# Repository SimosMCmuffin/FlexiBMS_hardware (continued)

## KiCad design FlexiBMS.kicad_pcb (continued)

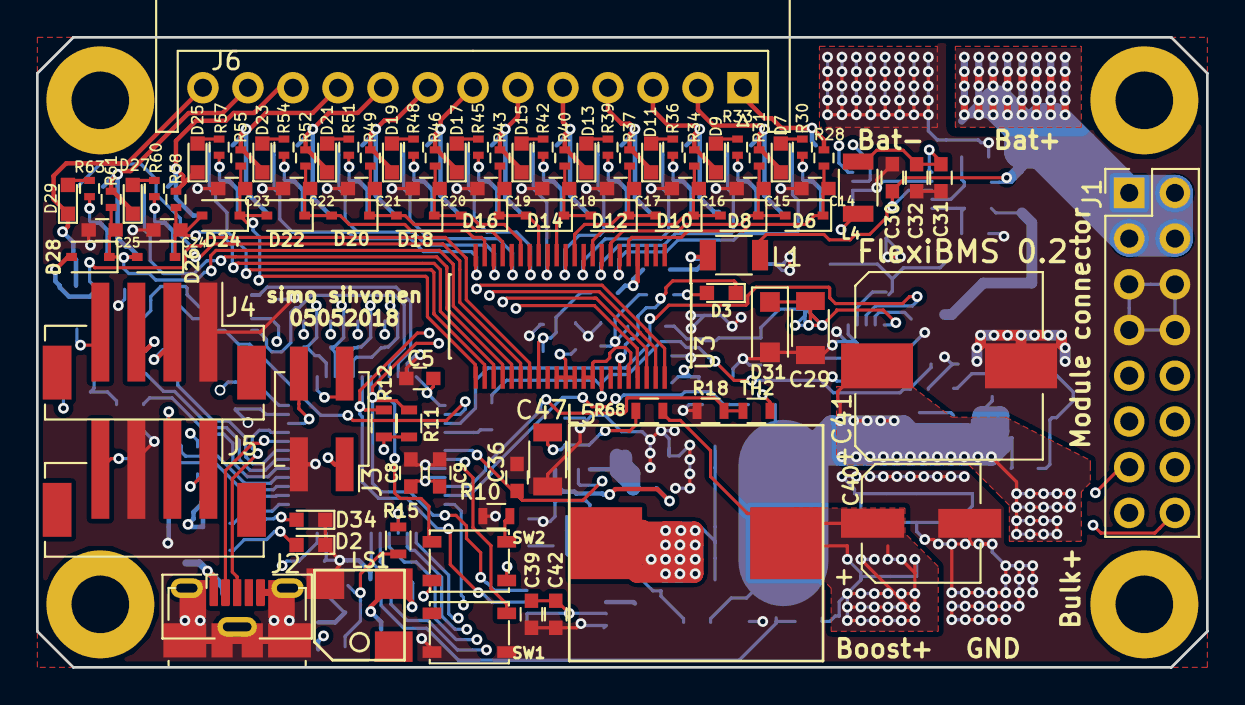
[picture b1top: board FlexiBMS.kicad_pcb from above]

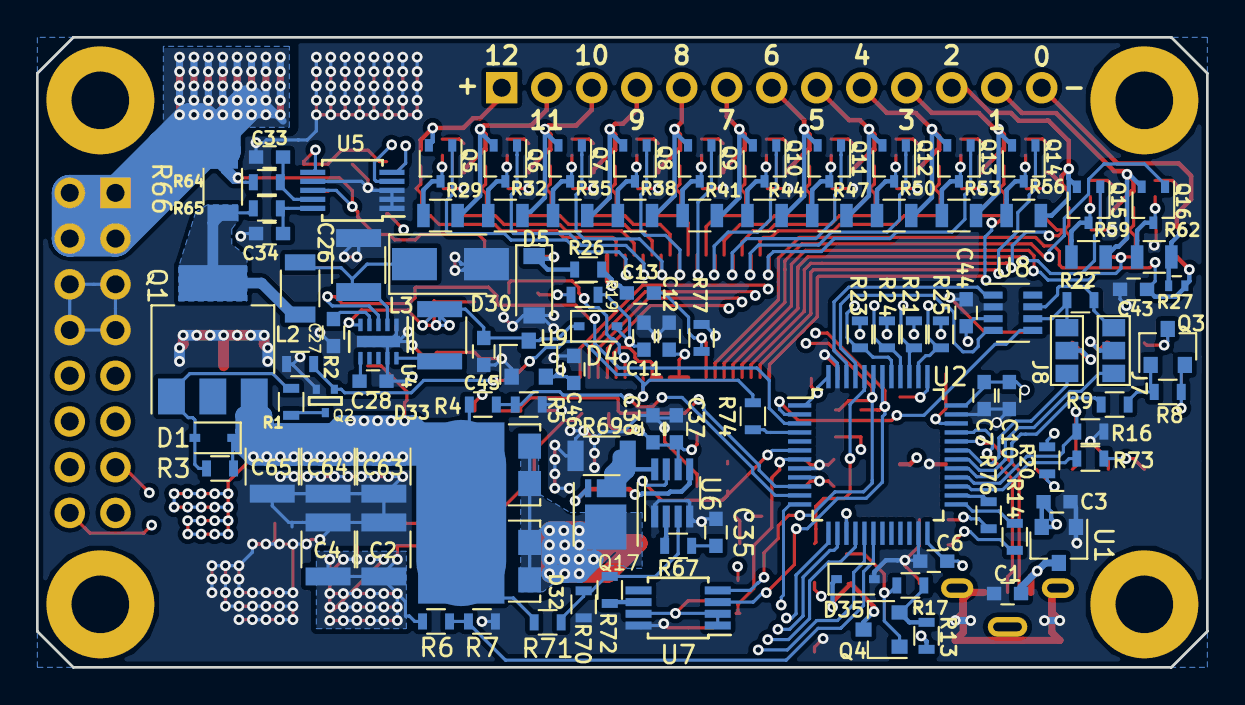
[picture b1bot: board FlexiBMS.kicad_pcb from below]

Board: 4 copper layers, 65.0 x 35.0 mm, 204 parts (107 on the bottom side), 142 nets.

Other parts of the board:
Q6, Q7, Q8, Q9, Q10, Q11, Q12, Q13, Q14, Q15, Q16: BSS84PW; SOT-323_SC-70

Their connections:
/LTC6803-3/cellBalance_1/BALANCE: Q16.1; also elsewhere on the board
/LTC6803-3/cellBalance_1/CELL+: Q16.2; also elsewhere on the board
/LTC6803-3/cellBalance_2/BALANCE: Q15.1; also elsewhere on the board
/LTC6803-3/cellBalance_2/CELL+: Q15.2; also elsewhere on the board
/LTC6803-3/cellBalance_3/BALANCE: Q14.1; also elsewhere on the board
/LTC6803-3/cellBalance_3/CELL+: Q14.2; also elsewhere on the board
/LTC6803-3/cellBalance_4/BALANCE: Q13.1; also elsewhere on the board
/LTC6803-3/cellBalance_4/CELL+: Q13.2; also elsewhere on the board
/LTC6803-3/cellBalance_5/BALANCE: Q12.1; also elsewhere on the board
/LTC6803-3/cellBalance_5/CELL+: Q12.2; also elsewhere on the board
/LTC6803-3/cellBalance_6/BALANCE: Q11.1; also elsewhere on the board
/LTC6803-3/cellBalance_6/CELL+: Q11.2; also elsewhere on the board
/LTC6803-3/cellBalance_7/BALANCE: Q10.1; also elsewhere on the board
/LTC6803-3/cellBalance_7/CELL+: Q10.2; also elsewhere on the board
/LTC6803-3/cellBalance_8/BALANCE: Q9.1; also elsewhere on the board
/LTC6803-3/cellBalance_8/CELL+: Q9.2; also elsewhere on the board
/LTC6803-3/cellBalance_9/BALANCE: Q8.1; also elsewhere on the board
/LTC6803-3/cellBalance_9/CELL+: Q8.2; also elsewhere on the board
/LTC6803-3/cellBalance_10/BALANCE: Q7.1; also elsewhere on the board
/LTC6803-3/cellBalance_10/CELL+: Q7.2; also elsewhere on the board
/LTC6803-3/cellBalance_11/BALANCE: Q6.1; also elsewhere on the board
/LTC6803-3/cellBalance_11/CELL+: Q6.2; also elsewhere on the board
unnamed 127: Q6.3; also elsewhere on the board
unnamed 128: Q7.3; also elsewhere on the board
unnamed 129: Q8.3; also elsewhere on the board
unnamed 130: Q9.3; also elsewhere on the board
unnamed 131: Q10.3; also elsewhere on the board
unnamed 132: Q11.3; also elsewhere on the board
unnamed 133: Q12.3; also elsewhere on the board
unnamed 134: Q13.3; also elsewhere on the board
unnamed 135: Q14.3; also elsewhere on the board
unnamed 136: Q15.3; also elsewhere on the board
unnamed 137: Q16.3; also elsewhere on the board

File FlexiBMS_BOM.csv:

Title,FlexiBMS
Revision,0.2
Date,2018-05-06
Generated,29.5.2018 21:36:46
Company,SiMoS MCmuffin / Simo Sihvonen
Comment 1,
Comment 2,
Comment 3,
Comment 4,
Total Parts,204
Total Unique Parts,56



Ref,Value,Qty,Footprint,Datasheet,B25/85,MFG,Power,TempCo.,Tol.,
"C1 C3 C5 C6 C7 C9 C11 C12 C27 C31 C37 C38 C39 C42 C44 C45 C46 C47 ","2µ2,16V",18,Capacitors_SMD:C_0603,, ,ANY, ,X5R, 
"C2 C4 C63 C64 C65 ","10µ,63V",5,Capacitors_SMD:C_1210,, ,ANY, ,X7R, 
"C8 C10 C13 C14 C15 C16 C17 C18 C19 C20 C21 C22 C23 C24 C25 C28 C30 C32 C33 C34 C43 ","100n,100V",21,Capacitors_SMD:C_0603,, ,ANY, ,X7R, 
"C26 ","1µ,63V",1,Capacitors_SMD:C_1210,, ,ANY, , , 
"C29 ","47µ,6V3",1,Capacitors_SMD:C_1206,, ,ANY, ,X5R, 
"C35 ","6n8,50V",1,Capacitors_SMD:C_0603,, ,ANY, ,X7R, 
"C36 ","10µ,16V",1,Capacitors_SMD:C_1206,, ,ANY, ,X7R, 
"C40 ","100µ,35V",1,Capacitors_SMD:CP_Elec_6.3x7.7,, ,EEE-FPV101XAP, , , 
"C41 ","100µ,63V",1,Capacitors_SMD:CP_Elec_10x10,, ,EEE-FK1J101P, , , 
"D1 ","12V",1,Diodes_SMD:D_SOD-323,, ,MM3Z12VT1G, , , 
"D2 D3 D7 D9 D11 D13 D15 D17 D19 D21 D23 D25 D27 D29 D34 ","LED",15,LEDs:LED_0603,, ,150060RS75000, , , 
"D4 D35 ","CUS520",2,Diodes_SMD:D_SOD-323,, ,CUS520 H3F, , , 
"D5 ","62V",1,Diodes_SMD:D_SOD-123,, ,CMHZ5265B TR, , , 
"D6 D8 D10 D12 D14 D16 D18 D20 D22 D24 D26 D28 ","7V5",12,Diodes_SMD:D_SOD-323,, ,MM3Z7V5T1G, , , 
"D30 ","53Vwm",1,Diodes_SMD:D_SMA,, ,P4SMA62A-E3/61, , , 
"D31 ","5,0Vwm",1,Diodes_SMD:D_SOD-123F,, ,SMF5.0, , , 
"D32 D33 ","FSV1060V",2,TO_SOT_Packages_SMD:TO-277A,, ,FSV1060V, , , 
"J1 ","Conn_02x08_Odd_Even",1,Pin_Headers:Pin_Header_Straight_2x08_Pitch2.54mm,, ,"PREC008DAAN-RC"/"PPTC082LFBN-RC"/"SFH210-PPPC-D08-ID-BK", , , 
"J2 ","USB_OTG",1,Connectors_USB:USB_Micro-B_Molex_47346-0001,, ,"10118192-0001LF" OR "1051330011", , , 
"J3 ","Conn_02x02",1,Socket_Strips:Socket_Strip_Straight_2x02_Pitch2.54mm_SMD,, ,M20-8750242, , , 
"J4 J5 ","JST_SMD_PH-04",2,Connectors_JST:JST_PH_B4B-PH-SM4-TB_04x2.00mm_Straight,, ,B4B-PH-SM4-TB(LF)(SN), , , 
"J6 ","JST_XH-13",1,Connectors_JST:JST_XH_S13B-XH-A_13x2.50mm_Angled,, ,"S13B-XH-A(LF)(SN)"/"B13B-XH-A(LF)(SN)", , , 
"J7 J8 ","GS3",2,Connectors:GS3,, ,SolderBridge, , , 
"L1 L2 L4 ","BLM31PG330SN1L",3,Inductors_SMD:L_1206,, ,BLM31PG330SN1L, , , 
"L3 ","22µ",1,Inductors_SMD:L_1210,, ,CBC3225T220MR, , , 
"L5 ","22µ,6.3A",1,Custom_footprints:HC9,, ,HC9-220-R, , , 
"LS1 ","Speaker",1,Custom_footprints:CSS-0575,, ,CSS-0575A-SMT-TR, , , 
"Q1 ","DMP6023LE-13",1,TO_SOT_Packages_SMD:SOT-223-3_TabPin2,, ,DMP6023LE-13, , , 
"Q2 ","DMN55D0UT-7",1,smd-semi:SOT-523,, ,DMN55D0UT-7, , , 
"Q3 Q4 ","PMV50XPR",2,TO_SOT_Packages_SMD:SOT-23,, ,PMV50XPR, , , 
"Q5 Q6 Q7 Q8 Q9 Q10 Q11 Q12 Q13 Q14 Q15 Q16 ","BSS84PW",12,TO_SOT_Packages_SMD:SOT-323_SC-70,, ,BSS84PWH6327XTSA1, , , 
"Q17 ","BSZ100N06NSATMA1",1,Custom_footprints:PG-TDSON-8,, ,BSZ100N06NSATMA1, , , 
"R1 R72 R74 ","36k",3,Resistors_SMD:R_0603,, ,ANY, , ,1%
"R2 R3 R71 ","510k",3,Resistors_SMD:R_0603,, ,ANY, , ,1%
"R4 R6 R21 R23 R25 ","1M",5,Resistors_SMD:R_0603,, ,ANY, , ,1%
"R5 R7 ","51k",2,Resistors_SMD:R_0603,, ,ANY, , ,1%
"R8 R17 ","220k",2,Resistors_SMD:R_0603,, ,ANY, , ,1%
"R9 R10 R15 R16 R18 R67 ","10k",6,Resistors_SMD:R_0603,, ,ANY, , ,1%
"R11 R12 R19 R24 R68 ","4k7",5,Resistors_SMD:R_0603,, ,ANY, , ,1%
"R13 R14 R20 R22 R26 R73 R76 R77 ","120R",8,Resistors_SMD:R_0603,, ,ANY, , ,1%
"R27 R28 R30 R31 R33 R34 R36 R37 R39 R40 R42 R43 R45 R46 R48 R49 R51 R52 R54 R55 R57 R58 R60 R61 R63 ","120R",25,Resistors_SMD:R_0402,, ,ANY, , ,1%
"R29 R32 R35 R38 R41 R44 R47 R50 R53 R56 R59 R62 ","51R",12,Resistors_SMD:R_0805,, ,ANY,0.5W, ,5%
"R64 R65 ","10R",2,Resistors_SMD:R_0603,, ,ANY, , ,1%
"R66 ","10m",1,Resistors_SMD:R_1206,, ,ANY,0.75W, ,1%
"R69 ","15m",1,Resistors_SMD:R_1206,, ,ANY,0.75W, ,1%
"R70 ","18k",1,Resistors_SMD:R_0603,, ,ANY, , ,1%
"SW1 SW2 ","SW_Push",2,Buttons_Switches_SMD:SW_SPST_PTS810,, ,PTS810 SJK 250 SMTR LFS, , , 
"TH2 ","10k",1,Resistors_SMD:R_0603,,4300K,NCP18XH103J03RB, , ,5%
"U1 U9 ","AP2210N-3.3",2,TO_SOT_Packages_SMD:SOT-23,, ,AP2210N-3.3TRG1, , , 
"U2 ","STM32L433CCT6",1,Housings_QFP:LQFP-48_7x7mm_Pitch0.5mm,, ,STM32L433CCT6, , , 
"U3 ","LTC6803-3",1,Custom_footprints:FSOP-44_5.3x13.0mm_Pitch0.5mm,, ,LTC6803IG-3#PBF, , , 
"U4 ","MAX17502F",1,Housings_DFN_QFN:DFN-10-1EP_2x3mm_Pitch0.5mm,, ,MAX17502FATB+T, , , 
"U5 ","ISL28022",1,Housings_SSOP:MSOP-10_3x3mm_Pitch0.5mm,, ,ISL28022FUZ-T7A, , , 
"U6 ","LTC3873",1,TO_SOT_Packages_SMD:TSOT-23-8,, ,LTC3873ETS8#TRMPBF, , , 
"U7 ","MAX5215",1,Housings_SSOP:MSOP-8_3x3mm_Pitch0.65mm,, ,MAX5215GUA+, , , 
"U8 ","TCAN330",1,TO_SOT_Packages_SMD:SOT-23-8,, ,TCAN330DCNR, , , 




BOM made with KICAD_BOM_WIZARD (https://github.com/HashDefineElectronics/KiCad_BOM_Wizard.git)
Generated 29.5.2018 21:36:46

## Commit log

2018-02-23 First prototype KiCad project files added -Changed the LTC6803-3 battery stack monitors schematic a little bit to conform better to it's datasheets reference design
2018-02-23 Removed some old and deprecated files not used in the current design.
2018-02-26 0.1 Version finalized Silkscreen has been optimized, gerber files have been generated and boards have been ordered
2018-05-11 HW 0.2 finalized schematic and pcb files, BOM needs to be checked
    Lots of major and little problems fixed found in the 0.1
    Major changes:
    -LTC6803-3 footprint changed to it's correct one
    -Boost converter layout and capacitor optimization
    -MCU switched from STM32F070CBT6 to ultra low power STM32L433CCT6 to improve sleep state power consumption
    -Button/LED + Comms connectors switched from THT JST-XH to SMD JST-PH
2018-05-11 Updated revision dates on schematic pages and replaced old .pdf of the schematics with up-to-date one
2018-05-29 Replacing old license
2018-05-29 New project license CC BY-NC-SA 4.0
    Project license changed from GNU GENERAL PUBLIC LICENSE to CREATIVE COMMONS Attribution-NonCommercial 4.0 International , as of 29.05.2018 , to better suite the project being a hardware based one.
2018-05-29 Update README.md
    Updated the projects description to be more in line with it's current status
2018-05-29 0.2 HW files finalized and repo cleaned up.
    -BOM is now up-to-date and available in .csv and .pdf formats
2018-05-29 Fixed wrong CC license
2018-05-30 Updated schematic .pdf added
2021-03-02 Update README.md
    Added description that this HW repo is not the Lite-version's HW files, but an earlier failed concept design's
